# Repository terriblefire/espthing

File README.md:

# espthing - GPL v2

THIS DESIGN IS PROVIDED BY THE COPYRIGHT HOLDERS AND CONTRIBUTORS "AS IS" AND ANY EXPRESS OR IMPLIED WARRANTIES, INCLUDING, BUT NOT LIMITED TO, THE IMPLIED WARRANTIES OF MERCHANTABILITY AND FITNESS FOR A PARTICULAR PURPOSE ARE DISCLAIMED. IT WILL PROBABLY BLOW YOUR COMPUTER AND HOUSE UP. 

A stupid ESP thing i made for Erik Hemming. Completely Untested.

Its an Amiga Serial Port to ESP01 breakout with the potential to power from the amiga serial port.

The Amiga Serial port says it can do 20mA at 12V. Which is likely sufficent to power the ESP01 and the MAX3232 @ 3.3v. In the event its not sufficient there is a breakout for the power supply and an optional diode is there to protect the Amiga.

In reality i would bet the 12v line can do better than 20mA.

# BOM

| Qty | Value                                | Device                               | Package     | Parts          | Description                          |
| --- | ------------------------------------ | ------------------------------------ | ----------- | -------------- | ------------------------------------ |
| 1   |                                      | DB25_FEMALEHP                        | F25HP       | X1             | 25 Pin Female Connector.             |
| 1   |                                      | PINHD-2X4                            | 2X04        | ESPHEADER      | 2 x 4 PIN HEADER                     |
| 2   | 0.1uF                                | CAP_CERAMIC1206                      | 1206        | C7, C8         | Ceramic Capacitors                   |
| 2   | 10uF                                 | CAP_CERAMIC1206                      | 1206        | C1, C2         | Ceramic Capacitors                   |
| 4   | 1uF                                  | C-EUC1206                            | 1206        | C3, C4, C5, C6 | 50V Capacitory                       |
| 1   | 22uF                                 | CPOL-USB                             | PANASONIC_B | C89            | POLARIZED CAPACITOR, American symbol |
| 1   | EXT12v                               | JUMPER-2PTH                          | 1X02        | 12VPWR         | Jumper                               |
| 1   | LM1117-3.3                           | V_REG_LM1117SOT223                   | SOT223      | IC2            | Voltage Regulator LM1117             |
| 1   | MAX3232                              | MAX2323SOIC16                        | SO16        | U1             | RS232 Transceiver                    |
| 1   | SMD-DIODE-SWITCHING-75V-150MA(D1206) | SMD-DIODE-SWITCHING-75V-150MA(D1206) | LED-1206    | D1             | 304040005                            |

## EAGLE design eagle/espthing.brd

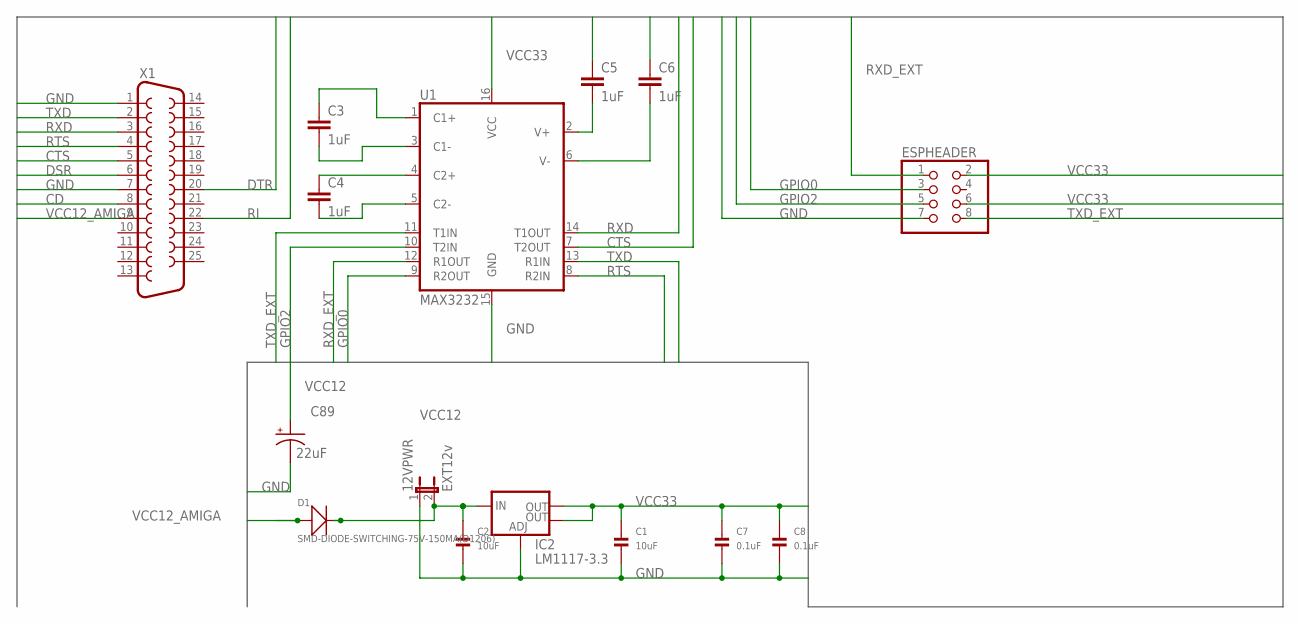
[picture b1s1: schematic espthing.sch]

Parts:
12VPWR: EXT12v; 1X02
C1, C2: 10uF; 1206
C3, C4, C5, C6: 1uF; C1206
C7, C8: 0.1uF; 1206
C89: 22uF; PANASONIC_B
D1: SMD-DIODE-SWITCHING-75V-150MA(D1206); LED-1206
ESPHEADER: PINHD-2X4; 2X04
IC2: LM1117-3.3; SOT223
U1: MAX3232; SO16
X1: DB25_FEMALEHP; F25HP

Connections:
CD: X1.8
CTS: U1.7 (T2OUT), X1.5
DSR: X1.6
DTR: X1.20
GND: 12VPWR.1, C1.2, C2.2, C5.1, C6.1, C7.2, C8.2, C89.-, ESPHEADER.7, IC2.1 (ADJ), U1.15 (GND), X1.1, X1.7
GPIO0: ESPHEADER.3, U1.9 (R2OUT)
GPIO2: ESPHEADER.5, U1.10 (T2IN)
unnamed: C3.1, U1.1 (C1+)
unnamed: C3.2, U1.3 (C1-)
unnamed: C4.1, U1.4 (C2+)
unnamed: C4.2, U1.5 (C2-)
unnamed: C5.2, U1.2 (V+)
unnamed: C6.2, U1.6 (V-)
RI: X1.22
RTS: U1.8 (R2IN), X1.4
RXD: U1.14 (T1OUT), X1.3
RXD_EXT: ESPHEADER.1, U1.12 (R1OUT)
TXD: U1.13 (R1IN), X1.2
TXD_EXT: ESPHEADER.8, U1.11 (T1IN)
VCC12: 12VPWR.2, C2.1, C89.+, D1.-, IC2.3 (IN)
VCC12_AMIGA: D1.+, X1.9
VCC33: C1.1, C7.1, C8.1, ESPHEADER.2, ESPHEADER.6, IC2.2 (OUT), IC2.4 (OUT), U1.16 (VCC)

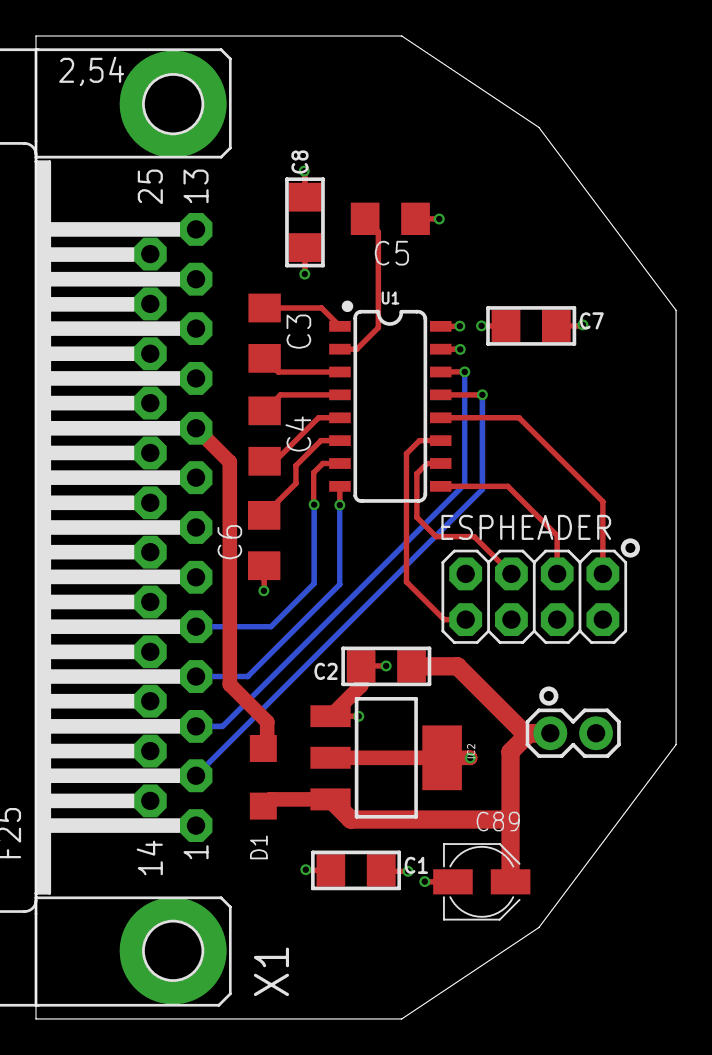
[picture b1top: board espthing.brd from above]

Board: 4 copper layers, 35.6 x 54.6 mm, 15 parts (0 on the bottom side), 18 nets.

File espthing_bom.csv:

"Qty";"Value";"Device";"Package";"Parts";"Description";"AVAILABILITY";"CHECK_PRICES";"DESCRIPTION";"MF";"MP";"PACKAGE";"POPULARITY";"PRICE";"PROD_ID";"PURCHASE-URL";"SNAPEDA_LINK";"SPICEPREFIX";"VALUE";
"1";"";"DB25_FEMALEHP";"F25HP";"X1";"25 Pin male connector. PCB edge mount for regular PCB thicknesses. This connector will connect directly to the back of a PC parallel port or through a normal DB25 extension cable (M/F). SKU: PRT-08287";"";"";"";"";"";"";"";"";"";"";"";"";"";
"1";"";"PINHD-2X4";"2X04";"ESPHEADER";"PIN HEADER";"";"";"";"";"";"";"";"";"";"";"";"";"";
"2";"0.1uF";"CAP_CERAMIC1206";"1206";"C7, C8";"Ceramic Capacitors";"";"";"";"";"";"";"";"";"";"";"";"";"";
"2";"10uF";"CAP_CERAMIC1206";"1206";"C1, C2";"Ceramic Capacitors";"";"";"";"";"";"";"";"";"";"";"";"";"";
"4";"1uF";"C-EUC1206";"C1206";"C3, C4, C5, C6";"CAPACITOR, European symbol";"";"";"";"";"";"";"54";"";"";"";"";"C";"";
"1";"22uF";"CPOL-USB";"PANASONIC_B";"C89";"POLARIZED CAPACITOR, American symbol";"";"";"";"";"";"";"";"";"";"";"";"";"";
"1";"EXT12v";"JUMPER-2PTH";"1X02";"12VPWR";"Jumper";"";"";"";"";"";"";"";"";"";"";"";"";"";
"1";"LM1117-3.3";"V_REG_LM1117SOT223";"SOT223";"IC2";"Voltage Regulator LM1117";"";"";"";"";"";"";"";"";"VREG-08170";"";"";"";"";
"1";"MAX3232";"MAX2323SOIC16";"SO16";"U1";"RS232 Transceiver";"";"";"";"";"";"";"";"";"IC-08171";"";"";"";"MAX3232";
"1";"SMD-DIODE-SWITCHING-75V-150MA(D1206)";"SMD-DIODE-SWITCHING-75V-150MA(D1206)";"LED-1206";"D1";"304040005 Check availability";"In Stock";"https://www.snapeda.com/parts/CD1206-S01575/Bourns+-+J.W.+Mi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";" CD1206-S01575, SMT Switching Diode, 100V 150mA, 4ns, 2-Pin 1206 | Bourns CD1206-S01575 ";"Bourns";"CD1206-S01575";"1206 Bourns";"";"None";"";"https://www.snapeda.com/api/url_track_click_mouser/?unipart_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";"https://www.snapeda.com/parts/CD1206-S01575/Bourns+-+J.W.+Mi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";"";"";

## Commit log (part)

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2023-11-15 initial untested commit
2023-11-15 added bom
2023-11-15 added images
2023-11-15 cleaned up bom
2025-10-27 adding gerber builder

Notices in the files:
parts and their libraries:
SparkFun-IC-Comms: Licensing: Creative Commons ShareAlike 4.0 International - https://creativecommons.org/licenses/by-sa/4.0
microbuilder: This work is placed in the public domain, and may be freely used for commercial and non-commercial work with the following conditions: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
